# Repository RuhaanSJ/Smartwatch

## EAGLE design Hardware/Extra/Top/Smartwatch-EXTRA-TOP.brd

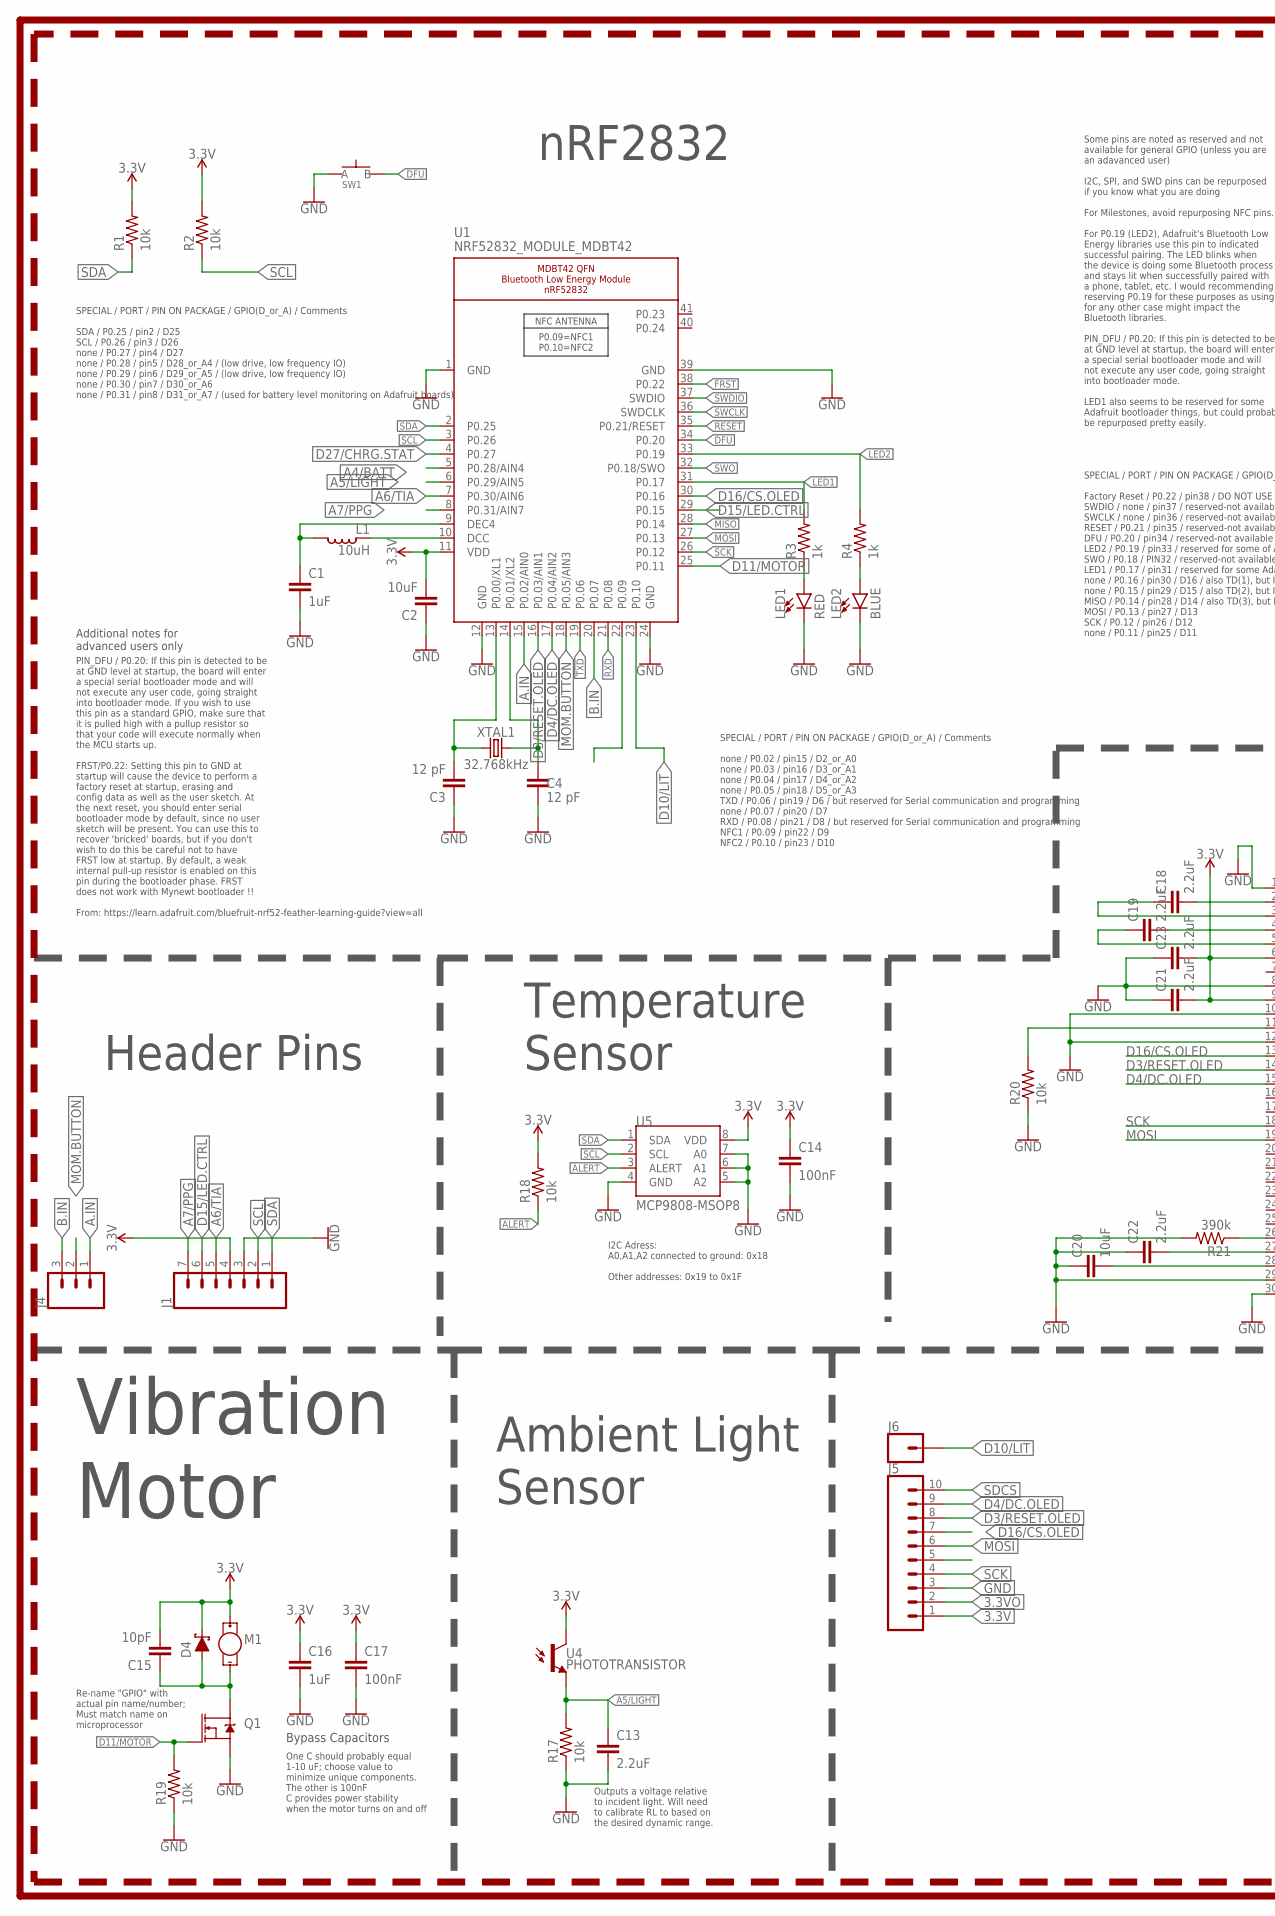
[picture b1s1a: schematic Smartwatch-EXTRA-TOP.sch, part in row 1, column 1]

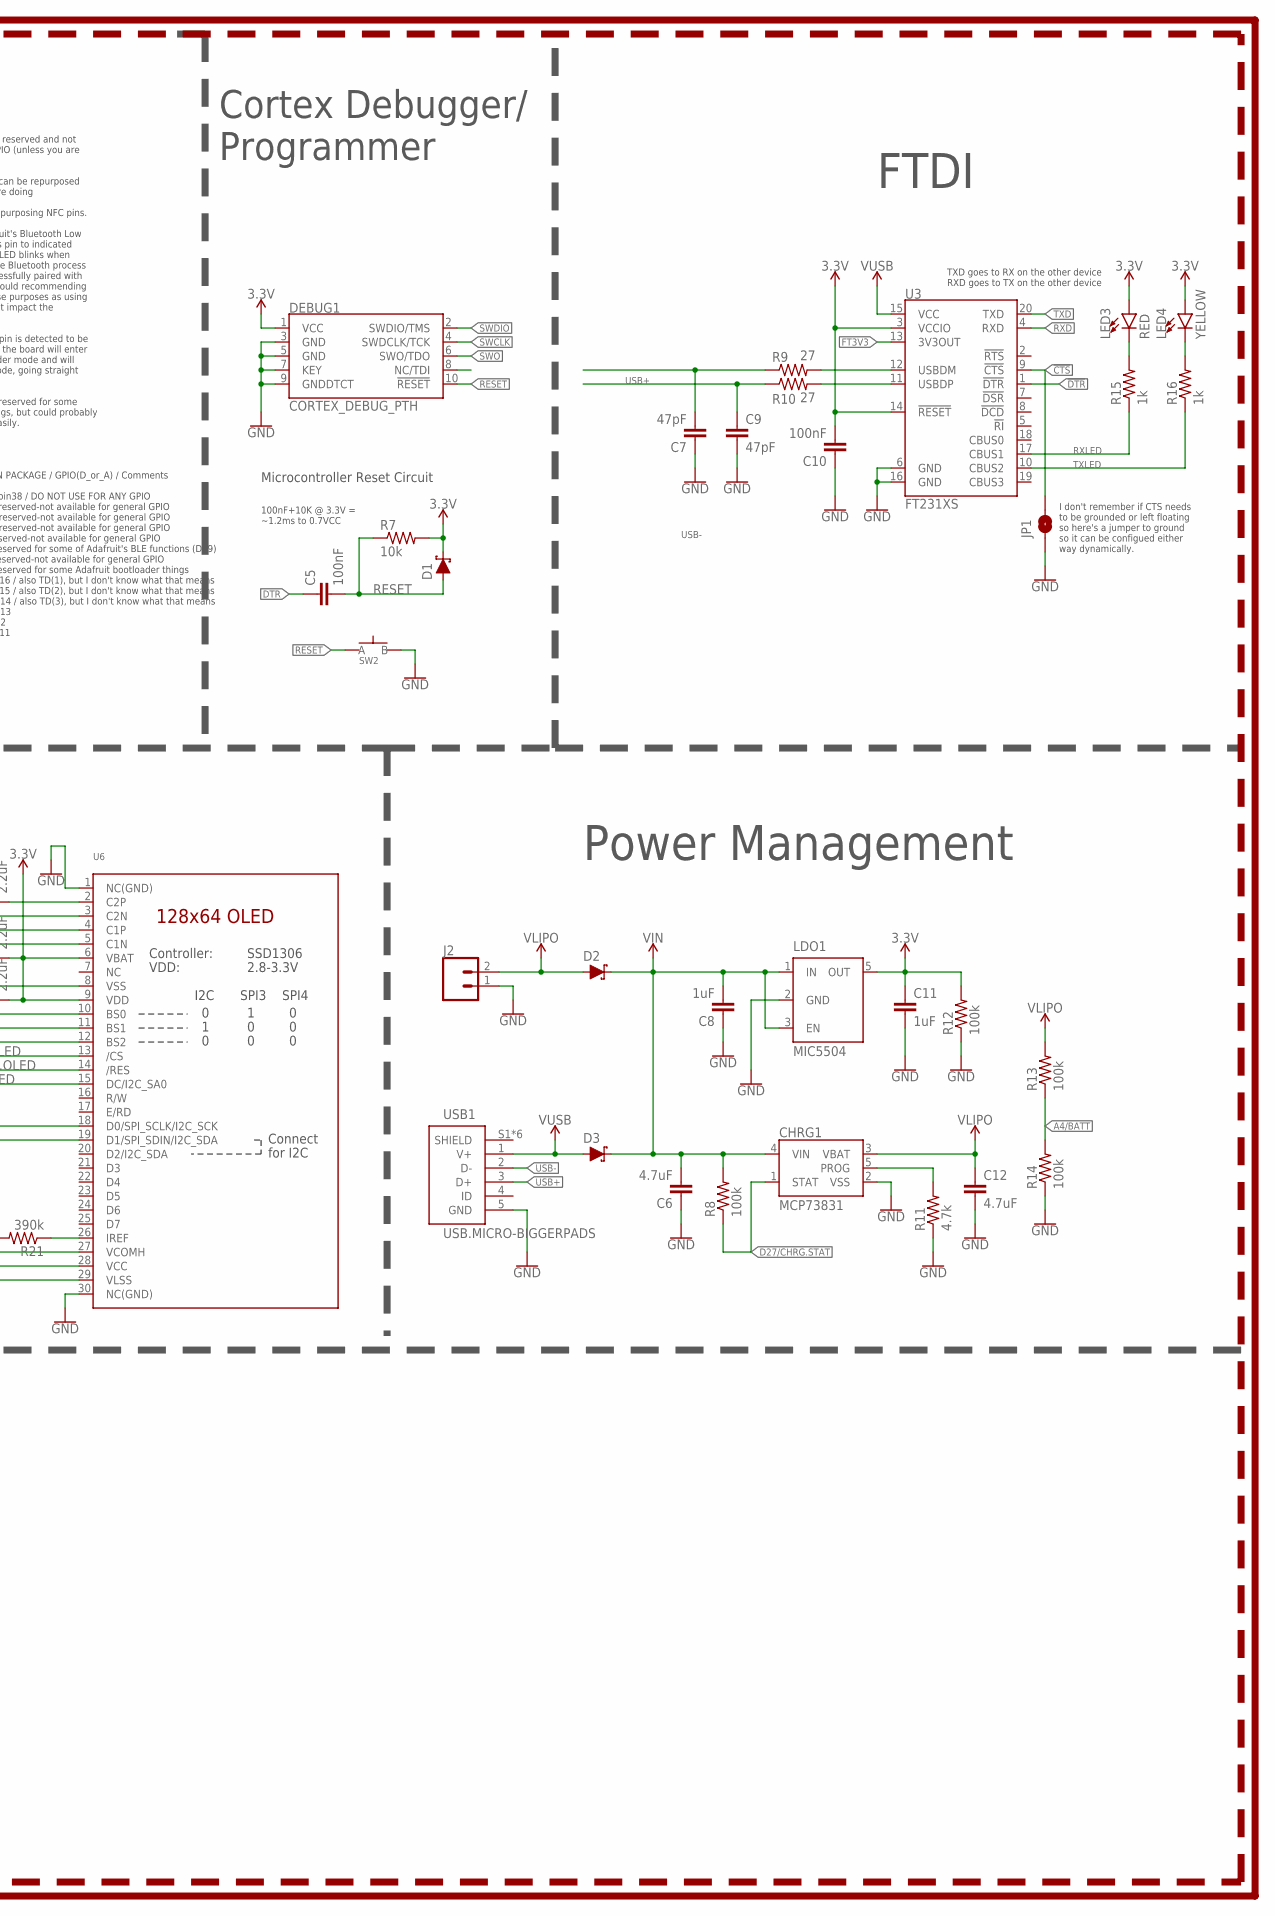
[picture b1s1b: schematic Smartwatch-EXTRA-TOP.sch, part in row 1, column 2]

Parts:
C1, C8, C11, C16: 1uF; C0603
C2: 10uF; C0805
C3, C4: 12 pF; C0603
C5, C10, C14, C17: 100nF; C0603
C6, C12: 4.7uF; C0603
C7, C9: 47pF; C0603
C13: 2.2uF; C0603
C15: 10pF; C0603
C18, C19, C21, C22, C23: 2.2uF; C0402
C20: 10uF; C0603
CHRG1: MCP73831; SOT23-5
D1, D2, D3, D4: SCHOTTKY-USC; USC
DEBUG1: CORTEX_DEBUG_PTH; 2X5-PTH-1.27MM
J1: CONN_07-1.27MM; 1X07_1.27MM
J2: CONN_02; 1X02
J4: CONN_03.50MIL; 1X03_1.27MM
J5: CONN_10; 1X10_NO_SILK
J6: CONN_01; 1X01
JP1: JUMPER-SMT_2_NO_SILK; SMT-JUMPER_2_NO_SILK
L1: 10uH; L0603
LDO1: MIC5504; SOT23-5
LED1, LED3: RED; LED-0603
LED2: BLUE; LED-0603
LED4: YELLOW; LED-0603
M1: VIB.MOTOR.C0720B015F; WIRE.LEADS
Q1: NFET-AO3404A; SOT23-3
R1, R2, R7, R17, R18, R19, R20: 10k; R0603
R3, R4, R15, R16: 1k; R0603
R8, R12, R13, R14: 100k; R0603
R9, R10: 27; R0603
R11: 4.7k; R0603
R21: 390k; R0603
SW1, SW2: SPST-PTS830GG140-COPY.1-3; BUTTON-GULLWING
U1: NRF52832_MODULE_MDBT42; BLE_MODULE_RAYTAC_MDBT42
U3: FT231XS; SSOP20_L
U4: PHOTOTRANSISTOR; R0603
U5: MCP9808-MSOP8; MSOP08
U6: DISP_OLED_UG-2864HSWEG01-NO-WRAPAROUND; UG-2864HSWEG01_0.96IN_NO-WRAPAROUND
USB1: USB.MICRO-BIGGERPADS; USB-MICRO-01.BIGGERPADS
XTAL1: 32.768kHz; 2-SMD.NOLEAD.2.0MMTO1.2MM

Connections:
3: J5.5
3.3V: C2.2, C10.2, C11.1, C14.1, C15.2, C16.1, C17.1, C21.2, C23.2, D1.- (C), D4.- (C), DEBUG1.1 (VCC), J1.4, J5.1, LDO1.5 (OUT), LED3.A, LED4.A, M1.+, R1.2, R2.2, R7.2, R12.2, R18.2, U1.11 (VDD), U3.3 (VCCIO), U3.14 (!RESET), U4.1 (C), U5.8 (VDD), U6.6 (VBAT), U6.9 (VDD)
3.3VO: J5.2
!CTS: JP1.2, U3.9 (!CTS)
!DTR: U3.1 (!DTR)
A4/BATT: R13.1, R14.2, U1.5 (P0.28/AIN4)
A5/LIGHT: C13.1, R17.2, U1.6 (P0.29/AIN5), U4.2 (E)
A6/TIA: J1.5, U1.7 (P0.30/AIN6)
A7/PPG: J1.7, U1.8 (P0.31/AIN7)
A.IN: J4.1, U1.15 (P0.02/AIN0)
ALERT: R18.1, U5.3 (ALERT)
B.IN: J4.3, U1.20 (P0.07)
D3/RESET.OLED: J5.8, U1.16 (P0.03/AIN1), U6.14 (/RES)
D4/DC.OLED: J5.9, U1.17 (P0.04/AIN2), U6.15 (DC/I2C_SA0)
D10/LIT: J6.1, U1.23 (P0.10)
D11/MOTOR: Q1.1 (G), R19.2, U1.25 (P0.11)
D15/LED.CTRL: J1.6, U1.29 (P0.15)
D16/CS.OLED: J5.7, U1.30 (P0.16), U6.13 (/CS)
D27/CHRG.STAT: CHRG1.1 (STAT), R8.1, U1.4 (P0.27)
DFU: SW1.3 (B), U1.34 (P0.20)
DTR: C5.1
FRST: U1.38 (P0.22)
FT3V3: U3.13 (3V3OUT)
GND: C1.2, C2.1, C3.1, C4.2, C6.1, C7.1, C8.1, C9.2, C10.1, C11.2, C12.2, C13.2, C14.2, C16.2, C17.2, C20.1, C21.1, C22.1, C23.1, CHRG1.2 (VSS), DEBUG1.3 (GND), DEBUG1.5 (GND), DEBUG1.7 (KEY), DEBUG1.9 (GNDDTCT), J1.3, J2.1, J5.3, JP1.1, LDO1.2 (GND), LED1.C, LED2.C, Q1.2 (S), R11.1, R12.1, R14.1, R17.1, R19.1, R20.1, R21.2, SW1.1 (A), SW2.3 (B), U1.1 (GND), U1.12 (GND), U1.24 (GND), U1.39 (GND), U3.6 (GND), U3.16 (GND), U5.4 (GND), U5.5 (A2), U5.6 (A1), U5.7 (A0), U6.1 (NC(GND)), U6.8 (VSS), U6.10 (BS0), U6.12 (BS2), U6.29 (VLSS), U6.30 (NC(GND)), USB1.5 (GND)
LED1: R3.2, U1.31 (P0.17)
LED2: R4.2, U1.33 (P0.19)
MISO: U1.28 (P0.14)
MOM.BUTTON: J4.2, U1.18 (P0.05/AIN3)
MOSI: J5.6, U1.27 (P0.13), U6.19 (D1/SPI_SDIN/I2C_SDA)
unnamed: C3.2, U1.13 (P0.00/XL1), XTAL1.P$1 (1)
unnamed: R20.2, U6.11 (BS1)
unnamed: C4.1, U1.14 (P0.01/XL2), XTAL1.P$2 (2)
unnamed: R21.1, U6.26 (IREF)
unnamed: C18.2, U6.2 (C2P)
unnamed: LED1.A, R3.1
unnamed: LED2.A, R4.1
unnamed: L1.1, U1.10 (DCC)
unnamed: C1.1, L1.2, U1.9 (DEC4)
unnamed: C18.1, U6.3 (C2N)
unnamed: C19.2, U6.4 (C1P)
unnamed: CHRG1.5 (PROG), R11.2
unnamed: C19.1, U6.5 (C1N)
unnamed: C15.1, D4.+ (A), M1.-, Q1.3 (D)
unnamed: C20.2, U6.28 (VCC)
unnamed: C22.2, U6.27 (VCOMH)
unnamed: R9.2, U3.12 (USBDM)
unnamed: R10.2, U3.11 (USBDP)
unnamed: LED3.C, R15.2
unnamed: LED4.C, R16.2
P0.09/NFC1: U1.22 (P0.09)
RESET: C5.2, D1.+ (A), DEBUG1.10 (!RESET), R7.1, SW2.1 (A), U1.35 (P0.21/RESET)
RXD: U1.21 (P0.08), U3.4 (RXD)
RXLED: R15.1, U3.17 (CBUS1)
SCK: J5.4, U1.26 (P0.12), U6.18 (D0/SPI_SCLK/I2C_SCK)
SCL: J1.2, R2.1, U1.3 (P0.26), U5.2 (SCL)
SDA: J1.1, R1.1, U1.2 (P0.25), U5.1 (SDA)
SDCS: J5.10
SWCLK: DEBUG1.4 (SWDCLK/TCK), U1.36 (SWDCLK)
SWDIO: DEBUG1.2 (SWDIO/TMS), U1.37 (SWDIO)
SWO: DEBUG1.6 (SWO/TDO), U1.32 (P0.18/SWO)
TXD: U1.19 (P0.06), U3.20 (TXD)
TXLED: R16.1, U3.10 (CBUS2)
USB+: C9.1, R10.1, USB1.3 (D+)
USB-: C7.2, R9.1, USB1.2 (D-)
VIN: C6.2, C8.2, CHRG1.4 (VIN), D2.- (C), D3.- (C), LDO1.1 (IN), LDO1.3 (EN), R8.2
VLIPO: C12.1, CHRG1.3 (VBAT), D2.+ (A), J2.2, R13.2
V_USB: D3.+ (A), U3.15 (VCC), USB1.1 (V+)

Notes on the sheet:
Microcontroller Reset Circuit
100nF+10K @ 3.3V = ~1.2ms to 0.7VCC
SPECIAL / PORT / PIN ON PACKAGE / GPIO(D_or_A) / Comments SDA / P0.25 / pin2 / D25 SCL / P0.26 / pin3 / D26 none / P0.27 / pin4 / D27 none / P0.28 / pin5 / D28_or_A4 / (low drive, low frequency IO) none / P0.29 / pin6 / D29_or_A5 / (low drive, low frequency IO) none / P0.30 / pin7 / D30_or_A6 none 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
SPECIAL / PORT / PIN ON PACKAGE / GPIO(D_or_A) / Comments none / P0.02 / pin15 / D2_or_A0 none / P0.03 / pin16 / D3_or_A1 none / P0.04 / pin17 / D4_or_A2 none / P0.05 / pin18 / D5_or_A3 TXD / P0.06 / pin19 / D6 / but reserved for Serial communication and programming none / P0.07 / pin20 / D7 RXD / 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
SPECIAL / PORT / PIN ON PACKAGE / GPIO(D_or_A) / Comments Factory Reset / P0.22 / pin38 / DO NOT USE FOR ANY GPIO SWDIO / none / pin37 / reserved-not available for general GPIO SWCLK / none / pin36 / reserved-not available for general GPIO RESET / P0.21 / pin35 / reserved-not available for general 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
Some pins are noted as reserved and not available for general GPIO (unless you are an adavanced user) I2C, SPI, and SWD pins can be repurposed if you know what you are doing For Milestones, avoid repurposing NFC pins. For P0.19 (LED2), Adafruit's Bluetooth Low Energy libraries use this pin to indic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
PIN_DFU / P0.20: If this pin is detected to be at GND level at startup, the board will enter a special serial bootloader mode and will not execute any user code, going straight into bootloader mode. If you wish to use this pin as a standard GPIO, make sure that it is pulled high with a pullup resis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
Additional notes for advanced users only
TXD goes to RX on the other device RXD goes to TX on the other device
I don't remember if CTS needs to be grounded or left floating so here's a jumper to ground so it can be configued either way dynamically.
Header Pins
nRF2832
Temperature Sensor
Cortex Debugger/ Programmer
FTDI
Power Management
Outputs a voltage relative to incident light. Will need to calibrate RL to based on the desired dynamic range.
I2C Adress: A0,A1,A2 connected to ground: 0x18 Other addresses: 0x19 to 0x1F
Bypass Capacitors
One C should probably equal 1-10 uF; choose value to minimize unique components. The other is 100nF C provides power stability when the motor turns on and off
Re-name "GPIO" with actual pin name/number; Must match name on microprocessor
Vibration Motor
Ambient Light Sensor

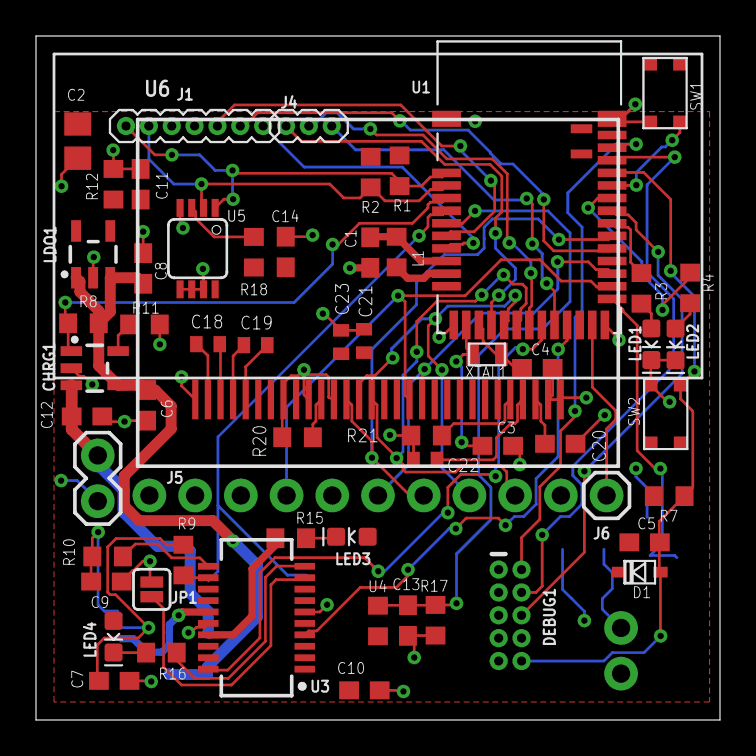
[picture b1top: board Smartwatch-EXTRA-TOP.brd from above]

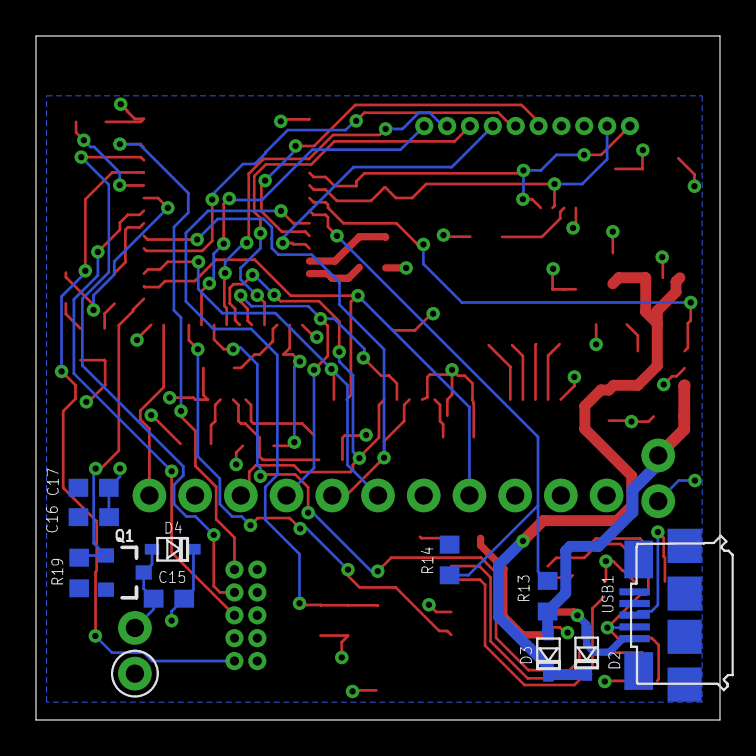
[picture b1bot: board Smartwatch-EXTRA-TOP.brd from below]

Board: 2 copper layers, 38.0 x 38.0 mm, 71 parts (12 on the bottom side), 58 nets.

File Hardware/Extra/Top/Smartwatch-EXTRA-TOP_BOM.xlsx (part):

Design Name -- Revision Code / Designer or Organization Name |  |  |  |  |  |  |  |  |  |  | Total | 32.518999999999998 | Total (in Bulk) | 27.297300000000003
BOM # | Comment | Designator | Description | Mounting Type | Package | Manufacturer | Manufacturer Part Number | Supplier | Supplier Part Number | Price per unit | Quantity | Total | Per 100 | Total
 | DigiKey
1 | NRF52832_MODULE_MDBT42 | U1 | Bluetooth Bluetooth v4.2 Transceiver Module 2.4GHz Integrated, Chip Surface Mou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 | SMD | 41-SMD Module | Seeed Technology Co., Ltd | 317030213 | Digi-Key | 1597-1434-ND | 10.1 | 1 | 10.1 | 10.1 | 10.1 | a
2 | FT231XS USB Serial | U3 | USB Bridge, USB to UART USB 2.0 UART Interface 20-SSOP | SMD | 20-SSOP | FTDI, Future Technology Devices International Ltd | FT231XS-U | Digi-Key | 768-1156-5-ND | 2.12 | 1 | 2.12 | 2.08 | 2.08 | a
3 | MIC5504-3.3V | LDO1 | Linear Voltage Regulator IC 1 Output 300mA SOT-23-5 | SMD | SOT23-5 | Microchip Technology | MIC5504-3.3YM5-TR | Digi-Key | 576-4764-1-ND | 0.11 | 1 | 0.11 | 0.08 | 0.08 | a
4 | MCP73831 T Li-Ion, Li-Pol Controller | CHRG1 | Charger IC Lithium-Ion/Polymer SOT-23-5 | SMD | SOT-23-5 | Microchip Technology | MCP73831T-2ACI/OT | Digi-Key | MCP73831T-2ACI/OTCT-ND | 0.56000000000000005 | 1 | 0.56000000000000005 | 0.44 | 0.44 | a
5 | CRYSTALECS-.327-12.5-12-C-TR (CRYSTAL) (32.7680kHz) | XTAL1 | 32.768kHz ±10ppm Crystal 12.5pF 90 kOhms 2-SMD, No Lead | SMD | 2-SMD, No Lead | ECS Inc. | ECS-.327-12.5-12-C-TR | Digi-Key | XC2288CT-ND | 0.59799999999999998 | 1 | 0.59799999999999998 | 0.54339999999999999 | 0.54339999999999999
6 | Cortex Debug Connector - 10 pin | DEBUG1 | Connector Header Through Hole 10 position 0.050" (1.27mm) | THT | NA | Amphenol ICC (FCI) | 20021111-00010T4LF | Digi-Key | 609-3712-ND | 0.69 | 1 | 0.69 | 0.52890000000000004 | 0.52890000000000004
7 | Schottky Diode | D1,D2,D3,D4 | Diode Schottky 30V 1.5A Surface Mount USC | SMD | USC | Toshiba Semiconductor and Storage | CUS15S30,H3F | Digi-Key | CUS15S30H3FCT-ND | 0.25600000000000001 | 5 | 1.28 | 0.12889999999999999 | 0.64449999999999996
8 | Red LED | LED1,LED3 | Red 622nm LED Indication - Discrete 2.2V 0603 (1608 Metric) | SMD | 0603 | Inolux | IN-S63ATR | Digi-Key | 1830-1065-1-ND | 0.17699999999999999 | 2 | 0.35399999999999998 | 8.6099999999999996E-2 | 0.17219999999999999
9 | Blue LED | LED2 | Blue 470nm LED Indication - Discrete 3V 0603 (1608 Metric) | SMD | 0603 | Inolux | IN-S63AT5B | Digi-Key | 1830-1061-1-ND | 0.17699999999999999 | 1 | 0.17699999999999999 | 8.6099999999999996E-2 | 8.6099999999999996E-2
10 | Yellow LED | LED4 | Yellow 590nm LED Indication - Discrete 2V 0603 (1608 Metric) | SMD | 0603 | Wurth Electronics Inc. | 150060YS75000 | Digi-Key | 732-4981-1-ND | 0.14000000000000001 | 1 | 0.14000000000000001 | 0.114 | 0.114
11 | Ambient Light Sensor | U4 | Optical Sensor Ambient 630nm Analog 0603 (1608 Metric) | SMD | 0603 | Inolux | IN-S63DTLS | Digi-Key | 1830-IN-S63DTLSCT-ND | 0.55000000000000004 | 1 | 0.55000000000000004 | 0.2586 | 0.2586
12 | MCP9808-MSOP8 | U5 | Temperature Sensor Digital, Local -40°C ~ 125°C 10 b 8-MSOP | SMD |  | Microchip Technology | MCP9808T-E/MS | Digi-Key | MCP9808T-E/MSTR-ND | 1.1299999999999999 | 1 | 1.1299999999999999 | 0.85 | 0.85
13 | NFET | Q1 | N-Channel 30V 500mA (Ta) 690mW (Ta) Surface Mount SOT-23-3 (TO-236) | SMD | SOT23-3 | ON Semiconductor | NTR4003NT3G | Digi-Key | NTR4003NT3GOSCT-ND | 0.27 | 1 | 0.27 | 9.1999999999999998E-2 | 9.1999999999999998E-2
14 | Vibration Motor | M1 | DC Motor Vibration, ERM 10000 RPM 3VDC | THT | Wire Leads | Jinlong Machinery & Electronics, Inc. | C0720B015F | Digi-Key | 1670-1030-ND | 3.54 | 1 | 3.54 | 2.6082000000000001 | 2.6082000000000001
15 | Micro USB | USB2 | USB - micro B USB 2.0 Receptacle Connector 5 Position Surface Mount, Right Angle | SMD | Flange, Horizontal | Amphenol FCI | 10118192-0001LF | Digi-Key | 609-4613-1-ND | 0.43 | 1 | 0.43 | 0.31580000000000003 | 0.31580000000000003
16 | CONN_07-1.27MM | J1,J3,J4 | 50 Positions Header Connector 0.050" (1.27mm) Through Hole Gold | THT |  | Sullins Connector Solutions | GRPB501VWVN-RC | Digi-Key | S9014E-50-ND | 3.11 | 3 | 9.33 | 2.4912000000000001 | 7.4736000000000002
17 | Tiny Rectangular Switch | SW1,SW2 | Tactile Switch SPST-NO Top Actuated Surface Mount | SMD | Gull Wing | C&K Components | PTS830GM140 SMTR LFS | Digi-Key | CKN10587CT-ND | 0.56999999999999995 | 2 | 1.1399999999999999 | 0.45500000000000002 | 0.91
18 | 10µH Inductor | L1 | 10µH Shielded Multilayer Inductor 250mA 1.05Ohm 0603 (1608 Metric) | SMD | 0603 | TDK Corporation | MLZ1608M100WTD25 | Digi-Key | MLZ1608M100WTD25 | 0.22 | 1 | 0.22 | 0.1346 | 0.1346
19 | 27 ohm resistor | R9, R10 | 27 Ohms ±1% 0.1W, 1/10W Chip Resistor 0603 (1608 Metric) Automotive AEC-Q200 Th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 | SMD | 0603 | Stackpole Electronics Inc | RMCF0603FT27R0 | Digi-Key | RMCF0603FT27R0CT-ND | 5.8999999999999999E-3 | 2 | 1.18E-2 | 6.7999999999999996E-3 | 1.3599999999999999E-2
20 | 1k Resistor | R3,R4,R15, R16 | 1 kOhms ±1% 0.1W, 1/10W Chip Resistor 0603 (1608 Metric) Automotive AEC-Q200 Th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 | SMD | 0603 | Stackpole Electronics Inc | RMCF0603FT1K00 | Digi-Key | RMCF0603FT1K00CT-ND | 5.8999999999999999E-3 | 4 | 2.3599999999999999E-2 | 6.7999999999999996E-3 | 2.7199999999999998E-2
21 | 10k Resistor | R1,R2,R5,R7,R17,R18,R19 | 10 kOhms ±1% 0.1W, 1/10W Chip Resistor 0603 (1608 Metric) Automotive AEC-Q200 T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 | SMD | 0603 | Stackpole Electronics Inc | RMCF0603FT10K0 | Digi-Key | RMCF0603FT10K0CT-ND | 5.8999999999999999E-3 | 6 | 3.5400000000000001E-2 | 6.7999999999999996E-3 | 4.0799999999999996E-2
22 | 100k Resistor | R8,R12,R13,R14 | 100 kOhms ±1% 0.1W, 1/10W Chip Resistor 0603 (1608 Metric) Automotive AEC-Q200 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 | SMD | 0603 | Stackpole Electronics Inc | RMCF0603FT100K | Digi-Key | RMCF0603FT100KCT-ND | 5.8999999999999999E-3 | 4 | 2.3599999999999999E-2 | 6.7999999999999996E-3 | 2.7199999999999998E-2
23 | 4.7k resistor | R11 | 4.7 kOhms ±1% 0.1W, 1/10W Chip Resistor 0603 (1608 Metric) Automotive AEC-Q200 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 | SMD | 0603 | Stackpole Electronics Inc | RMCF0603FT4K70 | Digi-Key | RMCF0603FT4K70CT-ND | 5.8999999999999999E-3 | 1 | 5.8999999999999999E-3 | 6.7999999999999996E-3 | 6.7999999999999996E-3
24 | 390k resistor | R6 | 390 kOhms ±1% 0.1W, 1/10W Chip Resistor 0603 (1608 Metric) Automotive AEC-Q200 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 | SMD | 0603 | Stackpole Electronics Inc | RMCF0603FG390K | Digi-Key | RMCF0603FG390KCT-ND | 5.8999999999999999E-3 | 2 | 1.18E-2 | 6.7999999999999996E-3 | 1.3599999999999999E-2
25 | 47 pF Capacitor | C7, C9 | 47pF ±5% 50V Ceramic Capacitor C0G, NP0 0603 (1608 Metric) | SMD | 0603 | Walsin Technology Corporation | 0603N470J500CT | Digi-Key | 1292-1528-1-ND | 1.0999999999999999E-2 | 2 | 2.1999999999999999E-2 | 6.7999999999999996E-3 | 1.3599999999999999E-2
26 | 12pF capacitor | C3,C4 | 12pF ±5% 50V Ceramic Capacitor C0G, NP0 0603 (1608 Metric) | SMD | 0603 | Walsin Technology Corporation | 0603N120J500CT | Digi-Key | 1292-1480-1-ND | 1.1900000000000001E-2 | 100 | 1.1900000000000002
27 | 100 nF Capacitor | C5,C10,C14,C17 | 0.1µF ±5% 16V Ceramic Capacitor X7R 0603 (1608 Metric) | SMD | 0603 | Yageo | CC0603JRX7R7BB104 | Digi-Key | 311-1776-1-ND | 3.3099999999999997E-2 | 4 | 0.13239999999999999 | 3.4299999999999997E-2 | 0.13719999999999999
28 | 1uF capacitor | C1,C8,C11,C16 | 1µF ±10% 25V Ceramic Capacitor X5R 0603 (1608 Metric) | SMD | 0603 | Samsung Electro-Mechanics | CL10A105KA8NNNC | Digi-Key | 1276-1102-1-ND | 0.1 | 4 | 0.4 | 1.8499999999999999E-2 | 7.3999999999999996E-2
29 | 2.2u capacitor | C13,C18,C19,C21,C22,C23 | 2.2µF ±10% 16V Ceramic Capacitor X5R 0603 (1608 Metric) | SMD | 0603 | Samsung Electro-Mechanics | CL10A225KO8NNNC | Digi-Key | 1276-1040-1-ND | 3.1600000000000003E-2 | 6 | 0.18960000000000002 | 3.3099999999999997E-2 | 0.1986
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
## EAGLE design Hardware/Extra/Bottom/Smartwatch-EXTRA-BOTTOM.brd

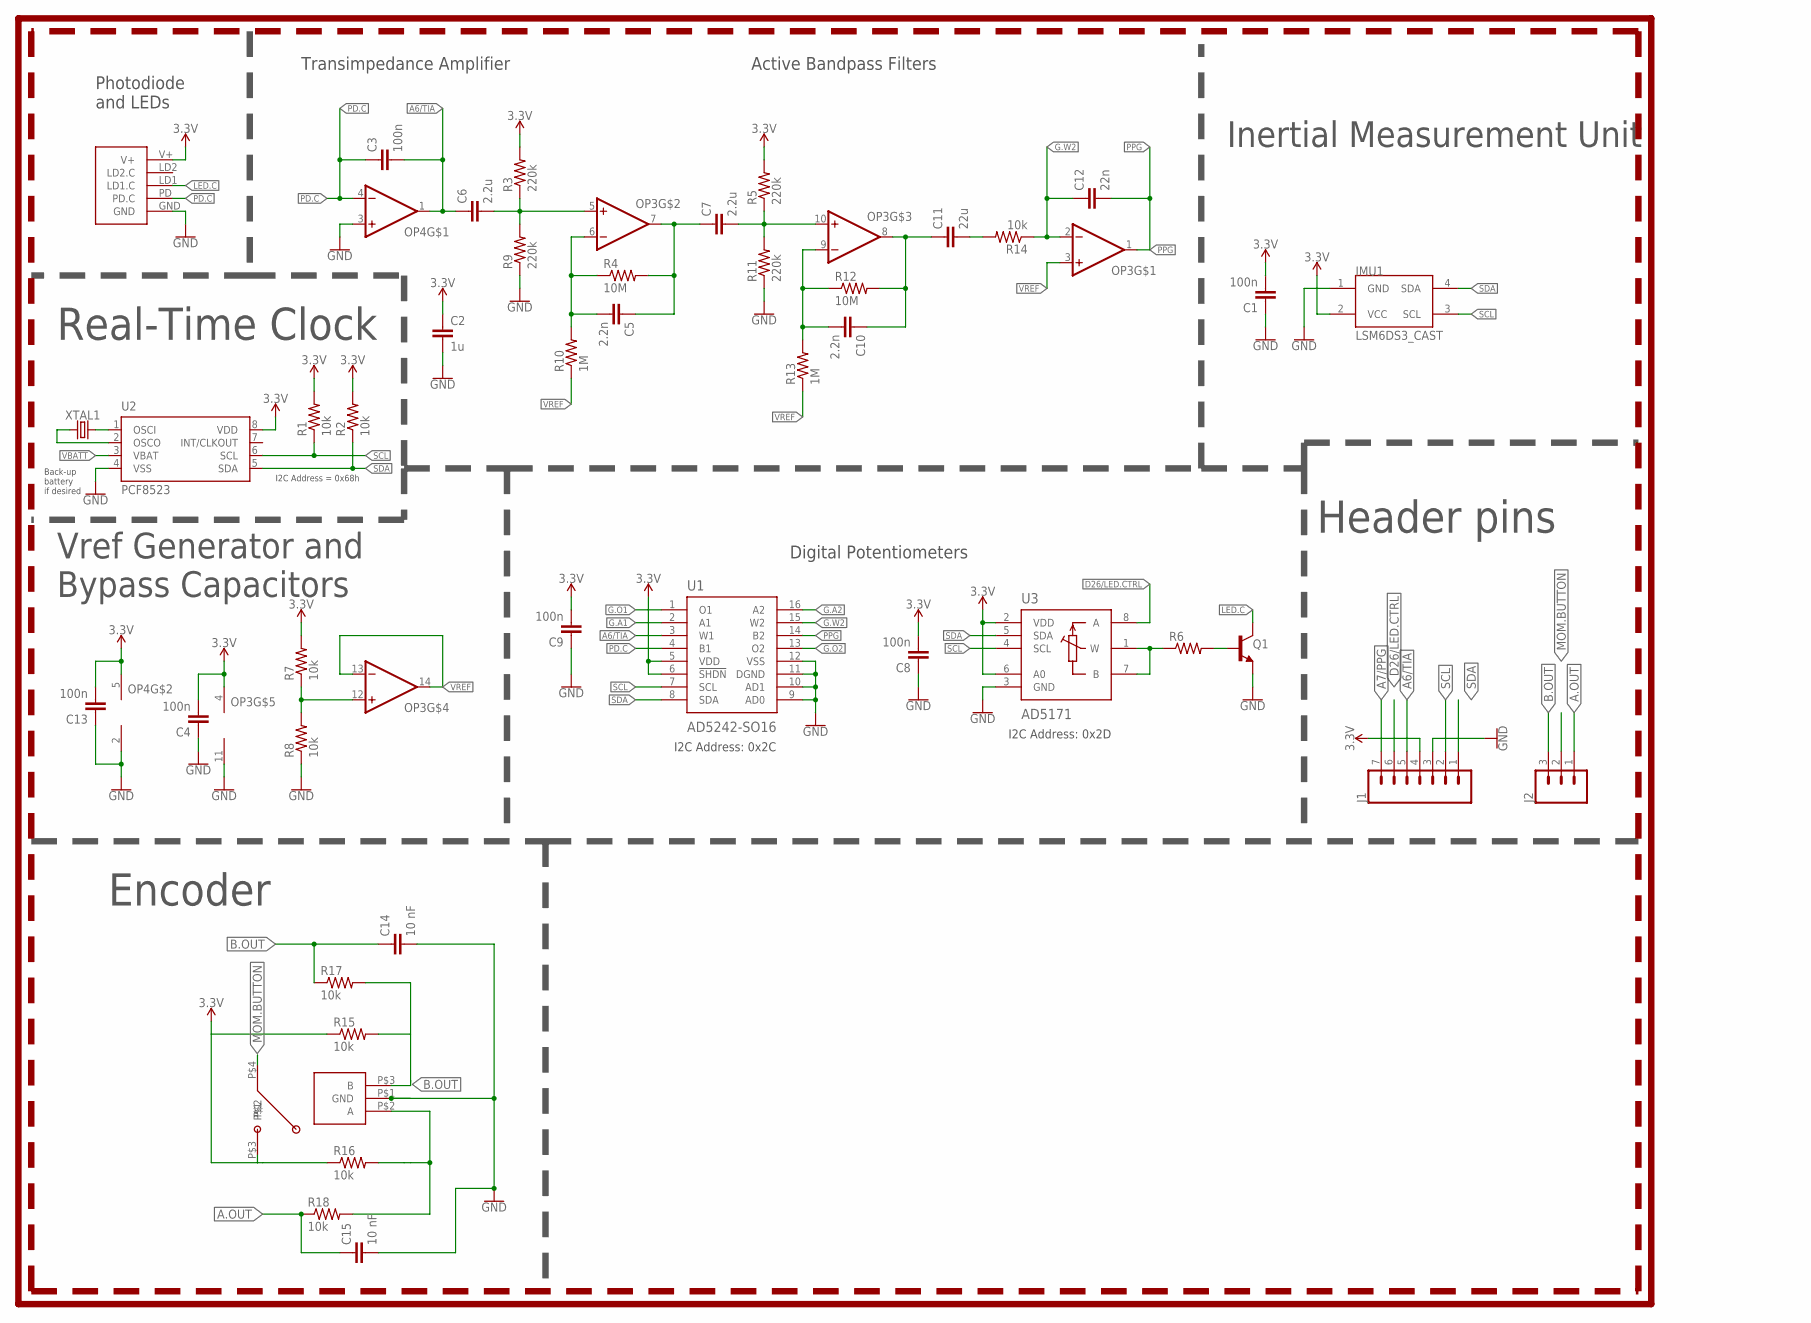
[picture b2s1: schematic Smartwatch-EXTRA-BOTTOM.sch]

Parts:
B1: SWITCH
C1, C3, C4, C8, C9, C13: 100n; C0603
C2: 1u; C0603
C5, C10: 2.2n; C0603
C6, C7: 2.2u; C0603
C11: 22u; C0603
C12: 22n; C0603
C14, C15: 10 nF; C0603
ENC1: EVQVU
IMU1: LSM6DS3_CAST
J1: CONN_07-1.27MM; 1X07_1.27MM
J2: CONN_03.50MIL; 1X03_1.27MM
OP3: OP-QUAD-SO14; SO14
OP4: OP-SINGLEOT; SOT23-5
Q1: NPN-GENERIC; SOT23-3
R1, R2, R14, R15, R16, R17, R18: 10k; R0603
R3, R5, R9, R11: 220k; R0603
R4, R12: 10M; R0603
R6: RESISTOR0603; R0603
R7, R8: 10k; R0402
R10, R13: 1M; R0603
U1: AD5242-SO16; SO16
U2: PCF8523; SO8; DIGIKEY 568-5306-1-ND
U3: AD5171; SOT-23-8
U4: PPG.MODULE.2
XTAL1: 32.7680kHz; 2-SMD.NOLEAD.2.0MMTO1.2MM

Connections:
3.3V: B1.P$3, C1.2, C2.1, C4.2, C8.2, C9.2, C13.2, IMU1.2 (VCC), J1.4, OP3.4 (V+), OP4.5 (V+), R1.2, R2.2, R3.2, R5.2, R7.2, R15.1, R16.1, U1.5 (VDD), U1.6 (!SHDN), U2.8 (VDD), U3.2 (VDD), U3.6 (A0), U4.V+
A6/TIA: C3.2, C6.1, J1.5, OP4.1 (OUT), U1.3 (W1)
A7/PPG: J1.7
A.OUT: C15.1, ENC1.P$2 (A), J2.1, R16.2, R18.1, R18.2
B.OUT: C14.1, ENC1.P$3 (B), J2.3, R17.1
D26/LED.CTRL: J1.6, U3.8 (A)
G.A1: U1.2 (A1)
G.A2: U1.16 (A2)
G.O1: U1.1 (O1)
G.O2: U1.13 (O2)
G.W2: C12.1, OP3.2 (-IN), R14.1, U1.15 (W2)
GND: C1.1, C2.2, C4.1, C8.1, C9.1, C13.1, C14.2, C15.2, ENC1.P$1 (GND), IMU1.1 (GND), J1.3, OP3.11 (V-), OP4.2 (V-), OP4.3 (+IN), Q1.2 (E), R8.1, R9.1, R11.1, U1.9 (AD0), U1.10 (AD1), U1.11 (DGND), U1.12 (VSS), U2.4 (VSS), U3.3 (GND), U4.GND
LED.C: Q1.3 (C), U4.LD1 (LD1.C)
MOM.BUTTON: B1.P$4, J2.2
unnamed: U2.2 (OSCO), XTAL1.P$1 (1)
unnamed: U2.1 (OSCI), XTAL1.P$2 (2)
unnamed: R15.2, R17.2
unnamed: Q1.1 (B), R6.2
unnamed: R6.1, U3.1 (W), U3.7 (B)
unnamed: OP3.12 (+IN), R7.1, R8.2
unnamed: C6.2, OP3.5 (+IN), R3.1, R9.2
unnamed: C5.2, OP3.6 (-IN), R4.1, R10.2
unnamed: C5.1, C7.1, OP3.7 (OUT), R4.2
unnamed: C7.2, OP3.10 (+IN), R5.1, R11.2
unnamed: C10.2, OP3.9 (-IN), R12.1, R13.2
unnamed: C10.1, C11.1, OP3.8 (OUT), R12.2
unnamed: C11.2, R14.2
PD.C: C3.1, OP4.4 (-IN), U1.4 (B1), U4.PD (PD.C)
PPG: C12.2, OP3.1 (OUT), U1.14 (B2)
SCL: IMU1.3 (SCL), J1.2, R1.1, U1.7 (SCL), U2.6 (SCL), U3.4 (SCL)
SDA: IMU1.4 (SDA), J1.1, R2.1, U1.8 (SDA), U2.5 (SDA), U3.5 (SDA)
VBATT: U2.3 (VBAT)
VREF: OP3.3 (+IN), OP3.13 (-IN), OP3.14 (OUT), R10.1, R13.1

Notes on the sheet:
Photodiode and LEDs
Active Bandpass Filters
Digital Potentiometers
Transimpedance Amplifier
I2C Address: 0x2C
I2C Address: 0x2D
I2C Address = 0x68h
Back-up battery if desired
Real-Time Clock
Vref Generator and Bypass Capacitors
Header pins
Inertial Measurement Unit
Encoder

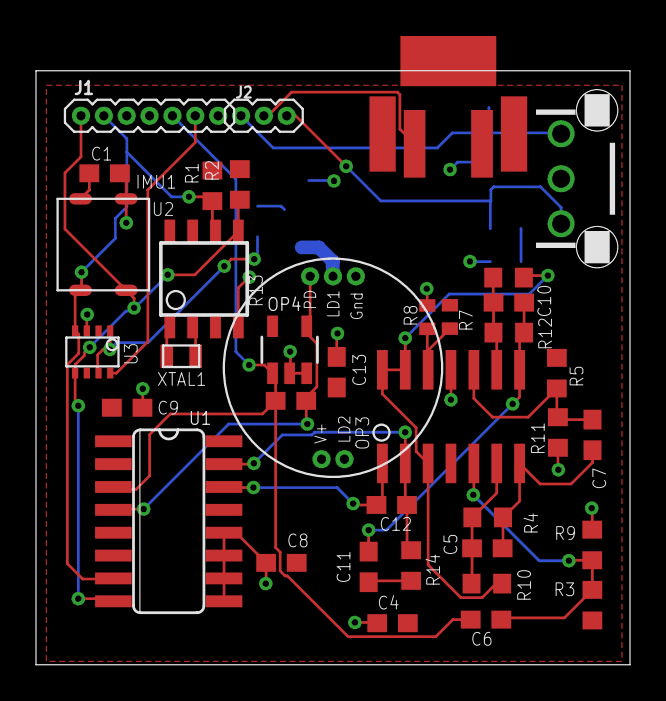
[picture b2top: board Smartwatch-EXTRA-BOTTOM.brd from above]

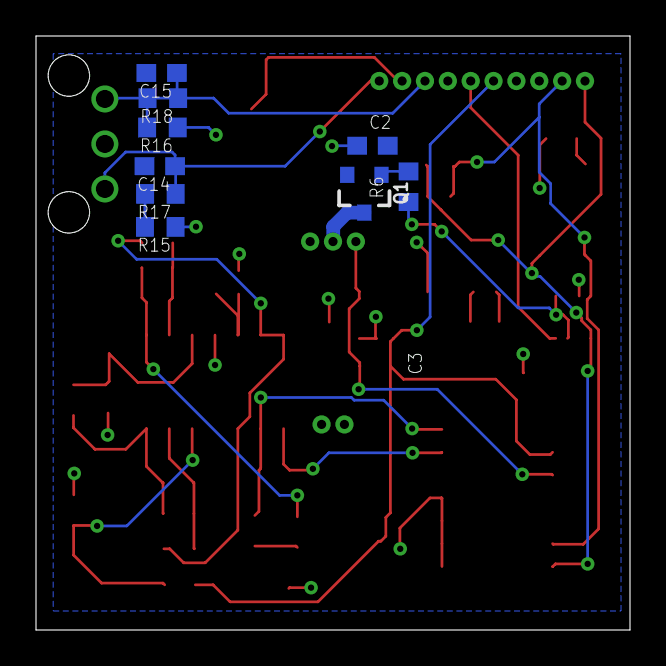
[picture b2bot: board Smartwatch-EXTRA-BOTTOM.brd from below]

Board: 2 copper layers, 33.0 x 33.0 mm, 46 parts (9 on the bottom side), 27 nets.

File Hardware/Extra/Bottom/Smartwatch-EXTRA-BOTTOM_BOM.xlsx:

Design Name -- Revision Code / Designer or Organization Name |  |  |  |  |  |  |  |  |  |  | Total | 12.407999999999999 | Total (in Bulk) | 5.1111000000000004
BOM # | Comment | Designator | Description | Mounting Type | Package | Manufacturer | Manufacturer Part Number | Supplier | Supplier Part Number | Price per unit | Quantity | Total | Per 100 | Total
 | DigiKey
1 | LSM6DS3 castellated breakout | IMU1 |  |  |  |  |  |  |  |  | 1 | 0 |  | 0
2 | MCP6001 |  | General Purpose Amplifier 1 Circuit Rail-to-Rail SOT-23-5 | SMD | SOT-23-5 | Microchip Technology | MCP6001T-E/OTCT-ND | Digi-Key | MCP6001T-E/OTCT-ND | 0.28999999999999998 | 1 | 0.28999999999999998 | 0.22 | 0.22
3 | Op Amp - MCP6004 | OP3 | General Purpose Amplifier 4 Circuit Rail-to-Rail 14-SOIC | SMD | 14-SOIC | Microchip Technology | MCP6004T-I/SL | Digi-Key | MCP6004T-I/SLCT-ND | 0.44 | 1 | 0.44 | 0.33 | 0.33
4 | TIA | OP4 | General Purpose Amplifier 1 Circuit Rail-to-Rail SOT-23-5 | SMD | SOT-23-5 | Microchip Technology | MCP6001T-I/OT | Digi-Key | MCP6001T-I/OTCT-ND | 0.24 | 1 | 0.24 | 0.18 | 0.18
5 | AD5242 | U1 | Digital Potentiometer 1M Ohm 2 Circuit 256 Taps I²C Interface 16-SOIC | SMD | 16-SOIC | Analog Devices Inc. | AD5242BRZ1M | Digi-Key | AD5242BRZ1M-ND | 3.47 | 1 | 3.47 | 2.7078000000000002 | 2.7078000000000002
6 | PCF8523 | U2 | Real Time Clock (RTC) IC Clock/Calendar I²C, 2-Wire Serial 8-SOIC (0.154", 3.90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 | SMD | 8-SO | NXP USA Inc. | PCF8523T/1,118 | Digi-Key | 568-5306-1-ND | 1.26 | 1 | 1.26 | 1.0881000000000001 | 1.0881000000000001
7 | NPN-Generic | Q1 | Bipolar (BJT) Transistor NPN 40V 600mA 300MHz 250mW Surface Mount TO-236AB | SMD | TO-236AB | Nexperia USA Inc. | PMBT2222A,215 | Digi-Key | 1727-2956-1-ND | 1.05 | 1 | 1.05 | 4.1799999999999997E-2 | 4.1799999999999997E-2
8 | CRYSTALECS-.327-12.5-12-C-TR (CRYSTAL) (32.7680kHz) | XTAL1 | 32.768kHz ±10ppm Crystal 12.5pF 90 kOhms 2-SMD, No Lead | SMD | 2-SMD, No Lead | ECS Inc. | ECS-.327-12.5-12-C-TR | Digi-Key | XC2288CT-ND | 0.59799999999999998 | 1 | 0.59799999999999998 | 0.54339999999999999 | 0.54339999999999999
55 | CONN_07-1.27MM (CONN_07) | J1,J2 | 50 Position Header Connector 0.050" (1.27mm) Through Hole Gold | THT |  | Sullins Connector Solutions | LPPB501NFFN-RC | Digi-Key | S9008E-50-ND | 5.0599999999999996 | 1 | 5.0599999999999996
56 | 10k Resistor | R1,R2,R7,R8,R14,R15,R16,R17,R18 | 10 kOhms ±1% 0.1W, 1/10W Chip Resistor 0603 (1608 Metric) Automotive AEC-Q200 T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 | SMD | 0603 | Stackpole Electronics Inc | RMCF0603FT10K0 | Digi-Key | RMCF0603FT10K0CT-ND | 5.8999999999999999E-3 | 9 | 5.3100000000000001E-2 | 6.7999999999999996E-3 | 6.1199999999999997E-2
57 | 220k resistor | R3,R5,R9,R11 | 220 kOhms ±1% 0.1W, 1/10W Chip Resistor 0603 (1608 Metric) Automotive AEC-Q200 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 | SMD | 0603 | Stackpole Electronics Inc | RMCF0603FT220K | Digi-Key | RMCF0603FT220KCT-ND | 5.8999999999999999E-3 | 4 | 2.3599999999999999E-2 | 6.7999999999999996E-3 | 2.7199999999999998E-2
58 | 1M Resistor | R10,R13 | 1 MOhms ±1% 0.1W, 1/10W Chip Resistor 0603 (1608 Metric) Automotive AEC-Q200 Th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 | SMD | 0603 | Stackpole Electronics Inc | RMCF0603FT1M00 | Digi-Key | RMCF0603FT1M00CT-ND | 5.8999999999999999E-3 | 2 | 1.18E-2 | 6.7999999999999996E-3 | 1.3599999999999999E-2
59 | 10M Resistor | R4,R12 | 10 MOhms ±1% 0.1W, 1/10W Chip Resistor 0603 (1608 Metric) Automotive AEC-Q200 T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 | SMD | 0603 | Stackpole Electronics Inc | RMCF0603FT10M0 | Digi-Key | RMCF0603FT10M0CT-ND | 8.8999999999999999E-3 | 2 | 1.78E-2 | 6.7999999999999996E-3 | 1.3599999999999999E-2
60 | 2.2n Capacitor | C5,C10 | 2200pF ±10% 50V Ceramic Capacitor X7R 0603 (1608 Metric) | SMD | 0603 | Walsin Technology Corporation | 0603B222K500CT | Digi-Key | 1292-1412-1-ND | 1.1599999999999999E-2 | 2 | 2.3199999999999998E-2 | 1.2200000000000001E-2 | 2.4400000000000002E-2
61 | 22n capacitor | C12 | 0.022µF ±10% 50V Ceramic Capacitor X7R 0603 (1608 Metric) | SMD | 0603 | Samsung Electro-Mechanics | CL10B223KB8NNNC | Digi-Key | 1276-1104-1-ND | 1.5599999999999999E-2 | 1 | 1.5599999999999999E-2 | 1.6299999999999999E-2 | 1.6299999999999999E-2
62 | 100 nF Capacitor | C1,C3,C4,C8,C9,C13 | 0.1µF ±5% 16V Ceramic Capacitor X7R 0603 (1608 Metric) | SMD | 0603 | Yageo | CC0603JRX7R7BB104 | Digi-Key | 311-1776-1-ND | 3.3099999999999997E-2 | 6 | 0.1986 | 3.4299999999999997E-2 | 0.20579999999999998
63 | 1uF capacitor | C2 | 1µF ±10% 25V Ceramic Capacitor X5R 0603 (1608 Metric) | SMD | 0603 | Samsung Electro-Mechanics | CL10A105KA8NNNC | Digi-Key | 1276-1102-1-ND | 0.1 | 1 | 0.1 | 1.8499999999999999E-2 | 1.8499999999999999E-2
64 | 2.2u capacitor | C6,C7 | 2.2µF ±10% 16V Ceramic Capacitor X5R 0603 (1608 Metric) | SMD | 0603 | Samsung Electro-Mechanics | CL10A225KO8NNNC | Digi-Key | 1276-1040-1-ND | 3.1600000000000003E-2 | 2 | 6.3200000000000006E-2 | 3.3099999999999997E-2 | 6.6199999999999995E-2
65 | 22u capacitor | C11 | 22µF ±20% 10V Ceramic Capacitor X5R 0603 (1608 Metric) | SMD | 0603 | Samsung Electro-Mechanics | CL10A226MP8NUNE | Digi-Key | 1276-1274-1-ND | 6.7199999999999996E-2 | 1 | 6.7199999999999996E-2 | 6.8400000000000002E-2 | 6.8400000000000002E-2
66 | 10 nF capacitor | C14,C15 | ±10% 16V Ceramic Capacitor X7R 0402 (1005 Metric) | SMD | 0604 | Samsung Electro-Mechanics | CL05B103KO5NNNC | Digi-Key | 1276-1051-2-ND | 0.1 | 2 | 0.2 | 7.4000000000000003E-3 | 1.4800000000000001E-2
67 | Encoder | ENC1 | Rotary Encoder Mechanical 12 Quadrature (Incremental) Vertical | THT |  | Panasonic Electronic Components | EVQ-VUA00112B | Digi-Key | P123413-ND | 1.18 | 1 | 1.18 | 0.80625000000000002 | 0.80625000000000002
68 | Tactile Button | B1 | SWITCH TACTILE SPST-NO 1VA 32V | SMD |  | C&K | KT11P2SA1M35LFG | Digi-Key | CKN1843CT-ND | 4.47 | 1 | 4.47 | 3.3904000000000001 | 3.3904000000000001
 | Mouser |  |  |  |  |  |  |  |  |  |  |  |  | 0
22 | AD5171 | U3 | Digital Potentiometer ICs IC 6-Bit OTP I2C | SMD | SOT-23-8 | Analog Devices | AD5171BRJZ100-R7 | Mouser | 584-AD5171BRJZ100-R7 | 2.68 | 1 | 2.68 | 1.82 | 1.82
